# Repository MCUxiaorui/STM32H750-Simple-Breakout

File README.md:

Except USB VBUS wrongly connected, everything else tested working.

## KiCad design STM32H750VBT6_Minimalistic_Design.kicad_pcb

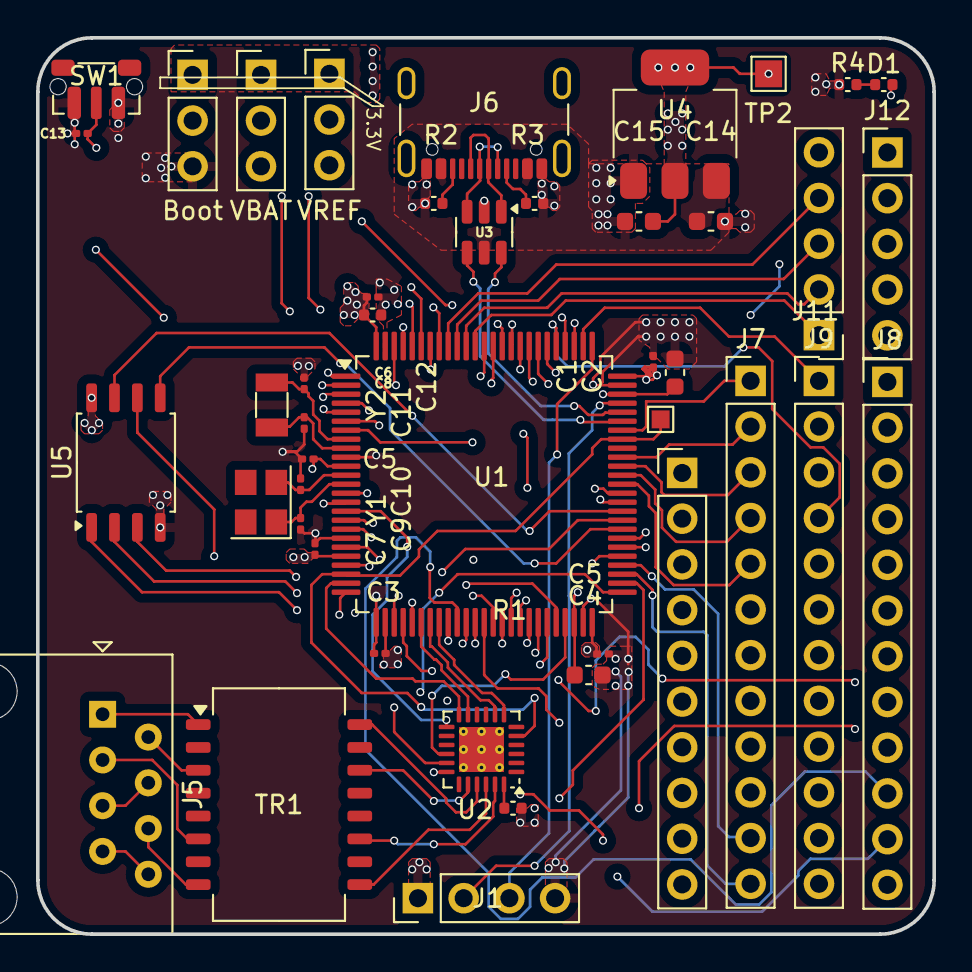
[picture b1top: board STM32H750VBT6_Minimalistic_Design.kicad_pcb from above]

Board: 6 copper layers, 49.8 x 49.8 mm, 44 parts (0 on the bottom side), 104 nets.

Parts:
C1, C3, C5, C5#2, C6, C7, C13: 100nF; C_0201_0603Metric
C2, C4: 2.2uF; C_0603_1608Metric
C8: 4.7uF; C_0402_1005Metric
C9, C10, C11, C12: 14pF; C_0201_0603Metric
C14, C15: 10uF; C_0603_1608Metric
D1: PC13_LED; C_0402_1005Metric
J1: St-Link; PinHeader_1x04_P2.54mm_Vertical
J2: Boot; PinHeader_1x03_P2.54mm_Vertical
J3: VBAT; PinHeader_1x03_P2.54mm_Vertical
J4: VREF; PinHeader_1x03_P2.54mm_Vertical
J5: RJ45_LED_Shielded; RJ45_Amphenol_54602-x08_Horizontal
J6: USB_C_Receptacle; USB_C_Receptacle_GCT_USB4105-xx-A_16P_TopMnt_Horizontal
J7, J8, J9: Conn_01x12_Pin; PinHeader_1x12_P2.54mm_Vertical
J10: Conn_01x10_Pin; PinHeader_1x10_P2.54mm_Vertical
J11, J12: Conn_01x05_Pin; PinHeader_1x05_P2.54mm_Vertical
R1: 12.1k; C_0402_1005Metric
R2, R3: 5.1K; C_0402_1005Metric
R4: 820R; C_0402_1005Metric
SW1: Reset; SW_Push_1P1T-MP_NO_Horizontal_Alps_SKRTLAE010
TP1: 50MHz_TP; TestPoint_Pad_1.0x1.0mm
TP2: 3V3_TP; TestPoint_Pad_1.5x1.5mm
TR1: TG110-E050N5xx; Transformer_Ethernet_Halo_N5_SO-16_7.11x12.7mm
U1: STM32H750VBTx; LQFP-100_14x14mm_P0.5mm
U2: LAN8742A; VQFN-24-1EP_4x4mm_P0.5mm_EP2.5x2.5mm_ThermalVias
U3: USBLC6-2SC6; SOT-23-6
U4: LM1117MP-3.3; SOT-223-3_TabPin2
U5: W25Q16JVSS; SOIC-8_5.23x5.23mm_P1.27mm
Y1: 24MHz_12pf; Crystal_SMD_3225-4Pin_3.2x2.5mm
Y2: 32.768KHz; Crystal_SMD_3215-2Pin_3.2x1.5mm

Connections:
+3.3V: C1.1, C3.1, C5.1, C5#2.1, C6.1, C7.1, C8.1, C15.1, J1.1, J2.1, J3.1, J4.1, TP2.1, U1.11 (VDD), U1.21 (VDDA), U1.27 (VDD), U1.50 (VDD), U1.75 (VDD), U1.100 (VDD), U4.2 (VO), U5.8 (VCC)
BOOT0: J2.2, U1.94 (BOOT0)
D+: J6.A6 (D+), J6.B6 (D+), U3.1 (I/O1)
D-: J6.A7 (D-), J6.B7 (D-), U3.3 (I/O2)
ETH_CRS_DV: U1.31 (PA7), U2.11 (CRS_DV/MODE2)
ETH_MDC: U1.16 (PC1), U2.13 (MDC)
ETH_MDIO: U1.24 (PA2), U2.12 (MDIO)
ETH_REF_CLK: TP1.1, U1.23 (PA1), U1.68 (PA9), U2.5 (XTAL1/CLKIN)
ETH_RXD0: U1.32 (PC4), U2.8 (RXD0/MODE0)
ETH_RXD1: U1.33 (PC5), U2.7 (RXD1/MODE1)
ETH_RXN: TR1.9 (RD+), U2.22 (RXN)
ETH_RXP: TR1.11 (RD-), U2.23 (RXP)
ETH_TXD0: U1.51 (PB12), U2.17 (TXD0)
ETH_TXD1: U1.52 (PB13), U2.18 (TXD1)
ETH_TXN: TR1.14 (TD+), U2.20 (TXN)
ETH_TXP: TR1.16 (TD-), U2.21 (TXP)
ETH_TX_EN: U1.47 (PB11), U2.16 (TXEN)
FS_USB_DN: U1.70 (PA11), U3.4 (I/O2)
FS_USB_DP: U1.71 (PA12), U3.6 (I/O1)
GND: C1.2, C2.2, C3.2, C4.2, C5.2, C5#2.2, C6.2, C7.2, C8.2, C9.2, C10.2, C11.2, C12.2, C13.2, C14.2, C15.2, J1.4, J2.3, J6.A1 (GND), J6.A12 (GND), J6.B1 (GND), J6.B12 (GND), R1.2, R2.1, R3.1, R4.2, SW1.1, U1.10 (VSS), U1.19 (VSSA), U1.26 (VSS), U1.49 (VSS), U1.74 (VSS), U1.99 (VSS), U2.25 (VSS), U3.2 (GND), U4.1 (GND), U5.4 (GND)
NRST: C13.1, SW1.2, U1.14 (NRST)
unnamed: D1.1 (K), R4.1
unnamed: J5.4, J5.5
unnamed: J5.7, J5.8
unnamed: J6.A5 (CC1), R3.2
unnamed: J6.B5 (CC2), R2.2
unnamed: J5.6, TR1.8 (RX+)
unnamed: J5.3, TR1.6 (RX-)
unnamed: J5.2, TR1.3 (TX+)
unnamed: J5.1, TR1.1 (TX-)
unnamed: R1.1, U2.24 (RBIAS)
OSC_IN_HSE: C10.1, U1.12 (PH0), Y1.2
OSC_IN_LSE: C12.1, U1.8 (PC14), Y2.2
OSC_OUT_HSE: C9.1, U1.13 (PH1), Y1.1
OSC_OUT_LSE: C11.1, U1.9 (PC15), Y2.1
PA0: J10.9, U1.22 (PA0)
PA3: J10.10, U1.25 (PA3)
PA4: J12.4, U1.28 (PA4)
PA5: J12.5, U1.29 (PA5)
PA6: J8.12, U1.30 (PA6)
PA10: J7.1, U1.69 (PA10)
PA15: J9.1, U1.77 (PA15)
PB0: J8.11, U1.34 (PB0)
PB1: J8.10, U1.35 (PB1)
PB3: J11.1, U1.89 (PB3)
PB4: J11.2, U1.90 (PB4)
PB5: J11.3, U1.91 (PB5)
PB6: J11.4, U1.92 (PB6)
PB7: J11.5, U1.93 (PB7)
PB8: J12.1, U1.95 (PB8)
PB9: J12.2, U1.96 (PB9)
PB14: J7.12, U1.53 (PB14)
PB15: J7.11, U1.54 (PB15)
PC0: J10.6, U1.15 (PC0)
PC2: J10.7, U1.17 (PC2_C)
PC3: J10.8, U1.18 (PC3_C)
PC6: J7.5, U1.63 (PC6)
PC7: J7.4, U1.64 (PC7)
PC8: J7.3, U1.65 (PC8)
PC9: J7.2, U1.66 (PC9)
PC10: J9.2, U1.78 (PC10)
PC11: J9.3, U1.79 (PC11)
PC12: J9.4, U1.80 (PC12)
PC13: D1.2 (A), U1.7 (PC13)
PD0: J9.5, U1.81 (PD0)
PD1: J9.6, U1.82 (PD1)
PD2: J9.7, U1.83 (PD2)
PD3: J9.8, U1.84 (PD3)
PD4: J9.9, U1.85 (PD4)
PD5: J9.10, U1.86 (PD5)
PD6: J9.11, U1.87 (PD6)
PD7: J9.12, U1.88 (PD7)
PD8: J7.10, U1.55 (PD8)
PD9: J7.9, U1.56 (PD9)
PD10: J7.8, U1.57 (PD10)
PD14: J7.7, U1.61 (PD14)
PD15: J7.6, U1.62 (PD15)
PE0: J12.3, U1.97 (PE0)
PE2: J10.1, U1.1 (PE2)
PE3: J10.2, U1.2 (PE3)
PE4: J10.3, U1.3 (PE4)
PE5: J10.4, U1.4 (PE5)
PE6: J10.5, U1.5 (PE6)
PE7: J8.9, U1.37 (PE7)
PE8: J8.8, U1.38 (PE8)
PE9: J8.7, U1.39 (PE9)
PE10: J8.6, U1.40 (PE10)
PE11: J8.5, U1.41 (PE11)
PE12: J8.4, U1.42 (PE12)
PE13: J8.3, U1.43 (PE13)
PE14: J8.2, U1.44 (PE14)
PE15: J8.1, U1.45 (PE15)
QSPI_BK1_IO0: U1.58 (PD11), U5.5 (DI(IO0))
QSPI_BK1_IO1: U1.59 (PD12), U5.2 (DO(IO1))
QSPI_BK1_IO2: U1.98 (PE1), U5.3 (IO2)
QSPI_BK1_IO3: U1.60 (PD13), U5.7 (IO3)
QSPI_BK1_NCS: U1.46 (PB10), U5.1 (~CS)
QSPI_CLK: U1.36 (PB2), U5.6 (CLK)
SWCLK: J1.3, U1.76 (PA14)
SWDIO: J1.2, U1.72 (PA13)
VBAT: J3.2, U1.6 (VBAT)
VBUS: C14.1, J6.A4 (VBUS), J6.A9 (VBUS), J6.B4 (VBUS), J6.B9 (VBUS), U3.5 (VBUS), U4.3 (VI)
VCAP: C2.1, C4.1, U1.48 (VCAP), U1.73 (VCAP)
VREF: J4.2, U1.20 (VREF+)

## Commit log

2025-01-11 Create md
